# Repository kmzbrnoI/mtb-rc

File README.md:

MTB-RC – MTBbus RailCom detector
================================

MTB-RC is a RailCom detector sending addresses of a detected mobile decoders
via MTBbus.

## Features

* 8 track sections.
* [MTBbus v4](https://mtb.kmz-brno.cz/) interface.
* Reading DCC addresses of mobile decoders.
* Galvanic separation of MTB & DCC.
* Single STM32F103 main MCU.
* MTB part power input: 8-20 V.
* DCC part powered directly from DCC.
* Several IO & power protections (ESD, overvoltage, switched polarity, ...).
* 4->1 track time multiplexing.
* Opensource & openhardware design.

## PCB

See [README in `pcb` subfolder](pcb/README.md).

## Firmware

See [README in `fw` subfolder](fw/README.md).

## Authors

* Kateřina Hanáková
* [Jan Horáček](mailto:jan.horacek@kmz-brno.cz)

## Licence

See README in subfolders for licenses regarding pcb design and firmware.

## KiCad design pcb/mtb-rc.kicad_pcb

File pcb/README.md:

MTB-RC PCB
==========

## Design

Schematics & PCB are designed in KiCad 7.

## Production

PCB is prepared to be automatically assembled in [JLCPCB](https://jlcpcb.com/).
SMD parts on **bottom** side should be assembled. Each SMD part has its `LCSC_ITEM`
attribute set.

```bash
$ make fab
```

## License

Content of this directory is provided under [Creative Commons
Attribution-ShareAlike 4.0
License](https://creativecommons.org/licenses/by-sa/4.0/) as openhardware
project. You may download any data, contribute to the project, create PCB
yourself or even sell it yourself.

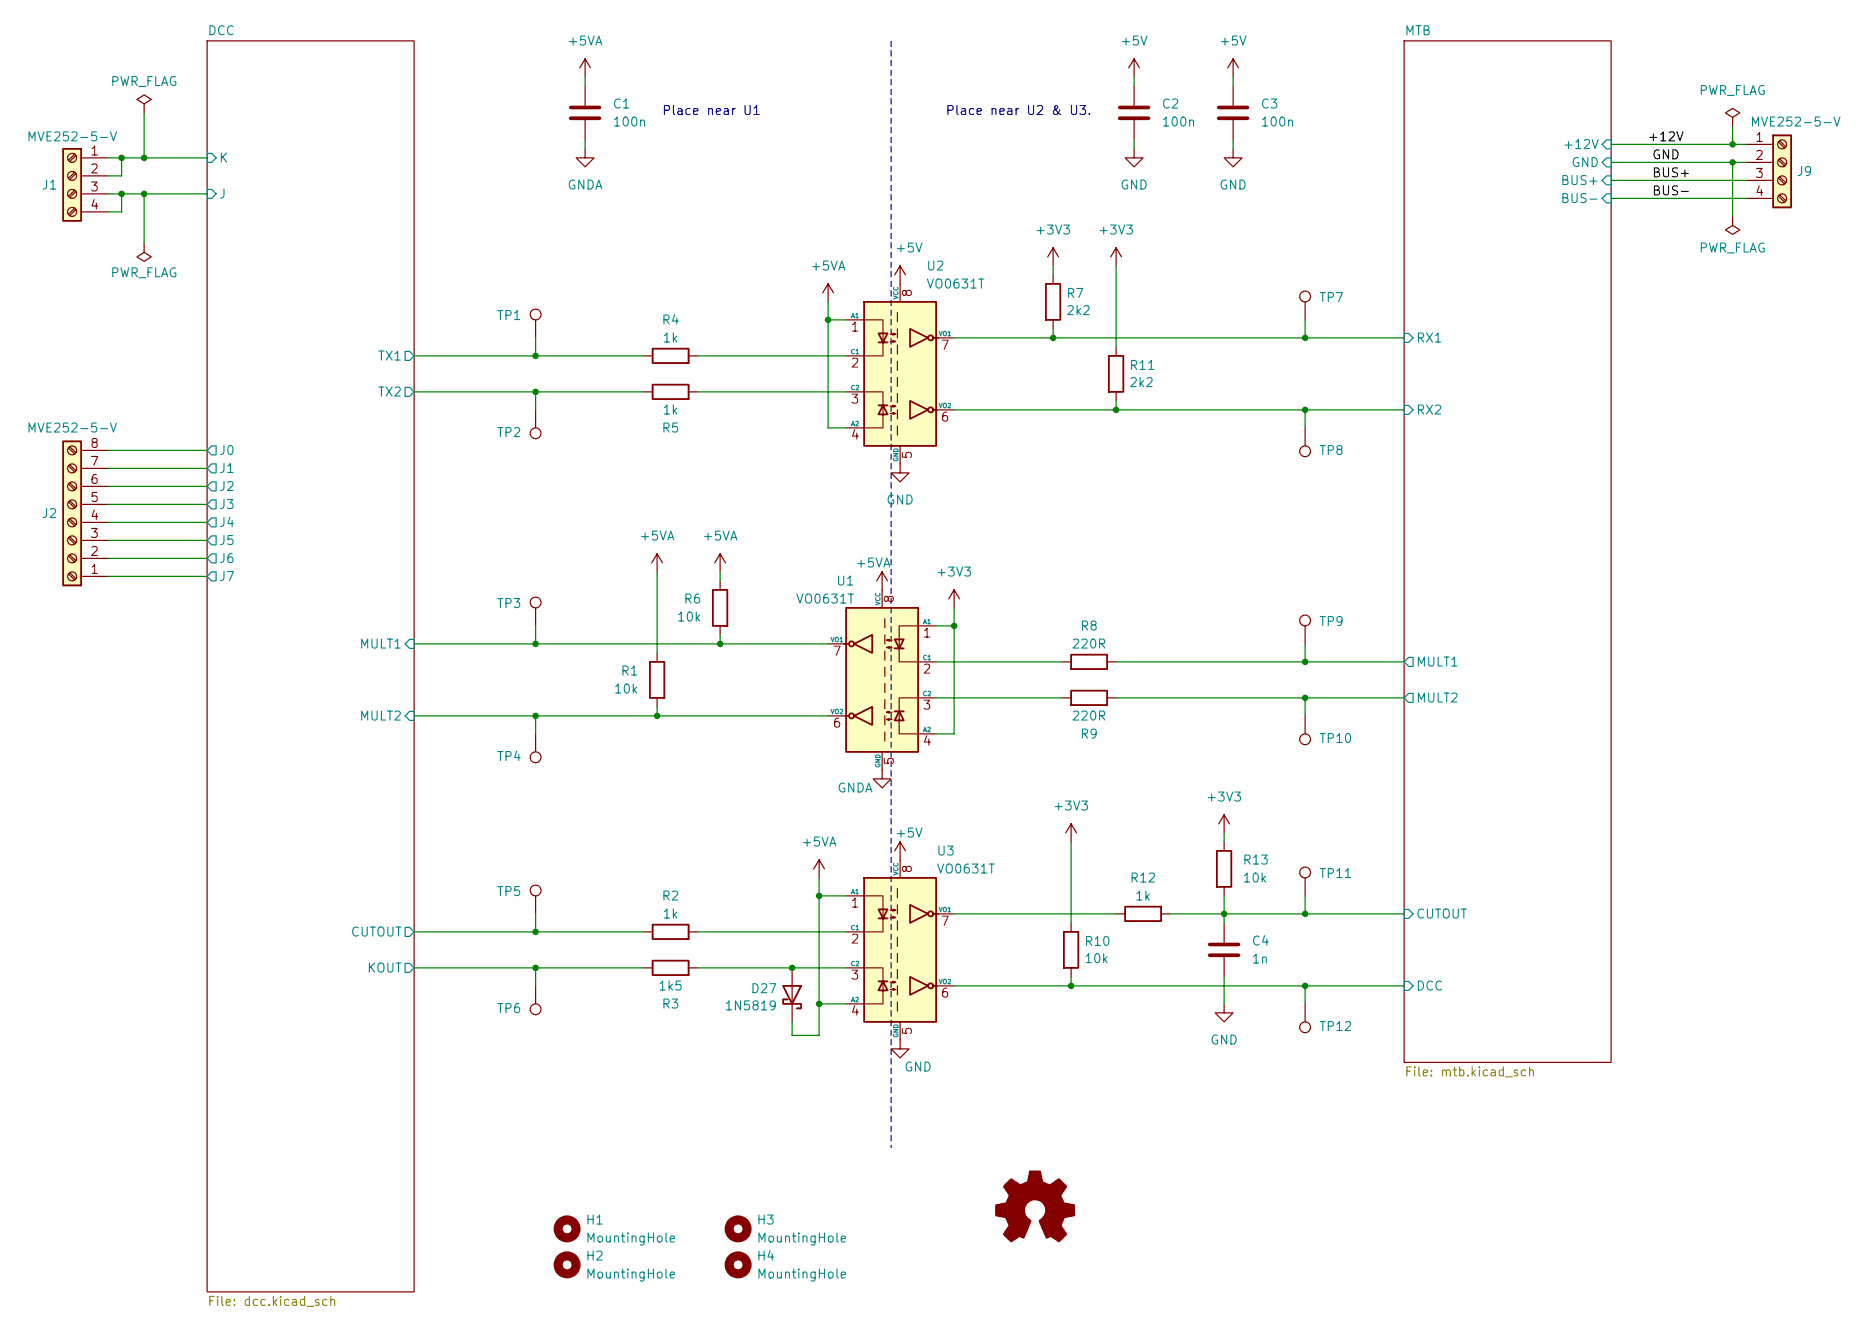
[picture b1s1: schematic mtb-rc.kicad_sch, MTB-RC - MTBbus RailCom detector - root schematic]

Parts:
C1, C2, C3: 100n; C_0805_2012Metric_Pad1.18x1.45mm_HandSolder
C4: 1n; C_0805_2012Metric_Pad1.18x1.45mm_HandSolder
D27: 1N5819; D_SOD-123
H1, H2, H3, H4: MountingHole; MountingHole_3.2mm_M3_Pad_Via
J1, J9: MVE252-5-V; MVE252-5-V-2x
J2: MVE252-5-V; MVE252-5-V-4x
R1, R6, R10, R13: 10k; R_0805_2012Metric_Pad1.20x1.40mm_HandSolder
R2, R4, R5, R12: 1k; R_0805_2012Metric_Pad1.20x1.40mm_HandSolder
R3: 1k5; R_0805_2012Metric_Pad1.20x1.40mm_HandSolder
R7, R11: 2k2; R_0805_2012Metric_Pad1.20x1.40mm_HandSolder
R8, R9: 220R; R_0805_2012Metric_Pad1.20x1.40mm_HandSolder
TP1, TP2, TP3, TP4, TP5, TP6, TP7, TP8, TP9, TP10, TP11, TP12: PinHeader_1x01_P2.54mm_Vertical
U1, U2, U3: VO0631T; SOIC-8_3.9x4.9mm_P1.27mm

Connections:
+3V3: R7.1, R10.1, R11.1, R13.1, U1.1 (A1), U1.4 (A2); also elsewhere on the board
+5V: C2.1, C3.1, U2.8 (VCC), U3.8 (VCC); also elsewhere on the board
+5VA: C1.1, D27.1 (K), R1.1, R6.1, U1.8 (VCC), U2.1 (A1), U2.4 (A2), U3.1 (A1), U3.4 (A2); also elsewhere on the board
/+12V: J9.1; also elsewhere on the board
/BUS+: J9.3; also elsewhere on the board
/BUS-: J9.4; also elsewhere on the board
/DCC/CUTOUT: R2.1, TP5.1; also elsewhere on the board
/DCC/J: J1.3, J1.4; also elsewhere on the board
/DCC/J0: J2.8; also elsewhere on the board
/DCC/J1: J2.7; also elsewhere on the board
/DCC/J2: J2.6; also elsewhere on the board
/DCC/J3: J2.5; also elsewhere on the board
/DCC/J4: J2.4; also elsewhere on the board
/DCC/J5: J2.3; also elsewhere on the board
/DCC/J6: J2.2; also elsewhere on the board
/DCC/J7: J2.1; also elsewhere on the board
/DCC/MULT1: R6.2, TP3.1, U1.7 (VO1); also elsewhere on the board
/DCC/MULT2: R1.2, TP4.1, U1.6 (VO2); also elsewhere on the board
/DCC/TX1: R4.1, TP1.1; also elsewhere on the board
/DCC/TX2: R5.1, TP2.1; also elsewhere on the board
/MTB/CUTOUT: C4.1, R12.2, R13.2, TP11.1; also elsewhere on the board
/MTB/DCC: R10.2, TP12.1, U3.6 (VO2); also elsewhere on the board
/MTB/MULT1: R8.1, TP9.1; also elsewhere on the board
/MTB/MULT2: R9.1, TP10.1; also elsewhere on the board
/MTB/RX1: R7.2, TP7.1, U2.7 (VO1); also elsewhere on the board
/MTB/RX2: R11.2, TP8.1, U2.6 (VO2); also elsewhere on the board
GND: C2.2, C3.2, C4.2, J9.2, U2.5 (GND), U3.5 (GND); also elsewhere on the board
GNDA: C1.2, U1.5 (GND); also elsewhere on the board
K: J1.1, J1.2; also elsewhere on the board
KOUT: R3.1, TP6.1; also elsewhere on the board
unnamed: D27.2 (A), R3.2, U3.3 (C2)
unnamed: R8.2, U1.2 (C1)
unnamed: R9.2, U1.3 (C2)
unnamed: R4.2, U2.2 (C1)
unnamed: R5.2, U2.3 (C2)
unnamed: R2.2, U3.2 (C1)
unnamed: R12.1, U3.7 (VO1)

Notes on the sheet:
Place near U2 & U3.
Place near U1

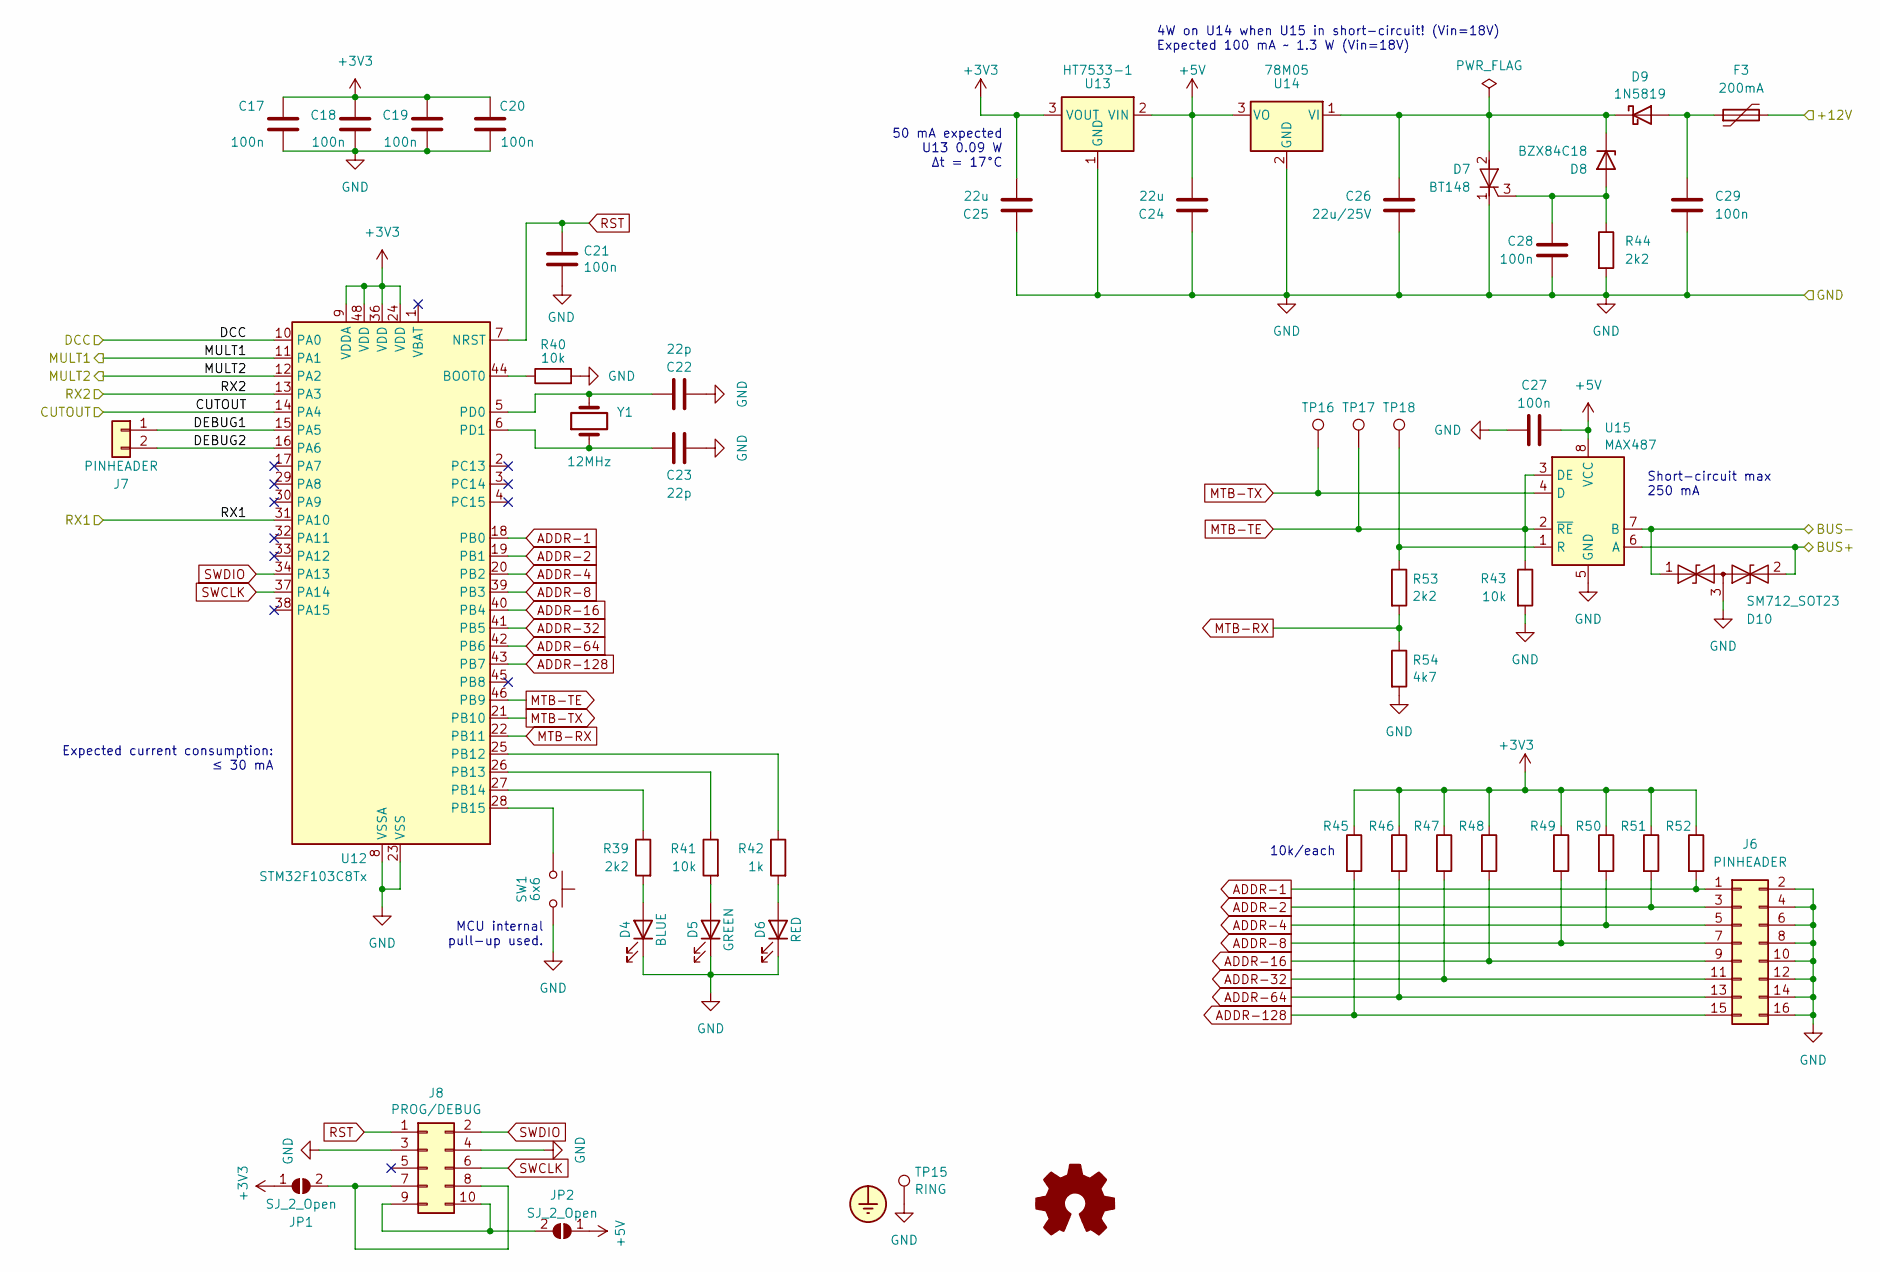
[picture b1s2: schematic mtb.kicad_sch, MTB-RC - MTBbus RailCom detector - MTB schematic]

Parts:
C17, C18, C19, C20, C27: 100n; C_0805_2012Metric_Pad1.18x1.45mm_HandSolder
C21: 100n; C_0805_2012Metric_Pad1.18x1.45mm_HandSolder; LCSC C49678
C22, C23: 22p; C_0805_2012Metric_Pad1.18x1.45mm_HandSolder
C24, C25: 22u; C_0805_2012Metric_Pad1.18x1.45mm_HandSolder
C26: 22u/25V; C_0805_2012Metric_Pad1.18x1.45mm_HandSolder
C28, C29: 100n; C_0805_2012Metric
D4: BLUE; LED_0805_2012Metric_Pad1.15x1.40mm_HandSolder
D5: GREEN; LED_0805_2012Metric_Pad1.15x1.40mm_HandSolder
D6: RED; LED_0805_2012Metric_Pad1.15x1.40mm_HandSolder
D7: BT148; SOT-223
D8: BZX84C18; SOT-23
D9: 1N5819; D_SOD-123
D10: SM712_SOT23; SOT-23
F3: 200mA; Fuse_1812_4532Metric_Pad1.30x3.40mm_HandSolder
J6: PINHEADER; PinHeader_2x08_P2.54mm_Vertical
J7: PINHEADER; PinHeader_1x02_P2.54mm_Vertical
J8: PROG/DEBUG; PinHeader_2x05_P2.54mm_Vertical; JLCPCB_IGNORE true
JP1, JP2: SJ_2_Open; PinHeader_1x02_P2.54mm_Vertical; JLCPCB_IGNORE true
R39, R44, R53: 2k2; R_0805_2012Metric_Pad1.20x1.40mm_HandSolder
R40, R41, R43, R45, R46, R47, R48, R49, R50, R51, R52: 10k; R_0805_2012Metric_Pad1.20x1.40mm_HandSolder
R42: 1k; R_0805_2012Metric_Pad1.20x1.40mm_HandSolder
R54: 4k7; R_0805_2012Metric_Pad1.20x1.40mm_HandSolder
SW1: 6x6; SW_PUSH_6mm_H4.3mm
TP15: RING; TestPoint_Loop_D1.80mm_Drill1.0mm_Beaded
TP16, TP17, TP18: PAD; PinHeader_1x01_P2.54mm_Vertical
U12: STM32F103C8Tx; LQFP-48_7x7mm_P0.5mm
U13: HT7533-1; SOT-89-3_Handsoldering
U14: 78M05; TO-252-2
U15: MAX487; DIP-8_W7.62mm_LongPads
Y1: 12MHz; Crystal_HC49-U_Vertical

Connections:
+3V3: C17.1, C18.1, C19.1, C20.1, C25.2, JP1.1 (A), R45.1, R46.1, R47.1, R48.1, R49.1, R50.1, R51.1, R52.1, U12.9 (VDDA), U12.24 (VDD), U12.36 (VDD), U12.48 (VDD), U13.3 (VOUT); also elsewhere on the board
+5V: C24.2, C27.1, JP2.1 (A), U13.2 (VIN), U14.3 (VO), U15.8 (VCC); also elsewhere on the board
/+12V: F3.2; also elsewhere on the board
/BUS+: D10.2 (A2), U15.6 (A); also elsewhere on the board
/BUS-: D10.1 (A1), U15.7 (B); also elsewhere on the board
/MTB/CUTOUT: U12.14 (PA4); also elsewhere on the board
/MTB/DCC: U12.10 (PA0); also elsewhere on the board
/MTB/DEBUG1: J7.1, U12.15 (PA5)
/MTB/DEBUG2: J7.2, U12.16 (PA6)
/MTB/MULT1: U12.11 (PA1); also elsewhere on the board
/MTB/MULT2: U12.12 (PA2); also elsewhere on the board
/MTB/RX1: U12.31 (PA10); also elsewhere on the board
/MTB/RX2: U12.13 (PA3); also elsewhere on the board
ADDR-1: J6.1, R52.2, U12.18 (PB0)
ADDR-2: J6.3, R51.2, U12.19 (PB1)
ADDR-4: J6.5, R50.2, U12.20 (PB2)
ADDR-8: J6.7, R49.2, U12.39 (PB3)
ADDR-16: J6.9, R48.2, U12.40 (PB4)
ADDR-32: J6.11, R47.2, U12.41 (PB5)
ADDR-64: J6.13, R46.2, U12.42 (PB6)
ADDR-128: J6.15, R45.2, U12.43 (PB7)
GND: C17.2, C18.2, C19.2, C20.2, C21.1, C22.2, C23.2, C24.1, C25.1, C26.2, C27.2, C28.2, C29.2, D4.1 (K), D5.1 (K), D6.1 (K), D7.1 (K), D10.3 (common), J6.2, J6.4, J6.6, J6.8, J6.10, J6.12, J6.14, J6.16, J8.3, J8.4, R40.2, R43.2, R44.2, R54.2, SW1.1, TP15.1, U12.8 (VSSA), U12.23 (VSS), U12.35 (VSS), U12.47 (VSS), U13.1 (GND), U14.2 (GND), U15.5 (GND); also elsewhere on the board
MTB-RX: R53.2, R54.1, U12.22 (PB11)
MTB-TE: R43.1, TP17.1, U12.46 (PB9), U15.2 (~RE), U15.3 (DE)
MTB-TX: TP16.1, U12.21 (PB10), U15.4 (D)
unnamed: D4.2 (A), R39.2
unnamed: D5.2 (A), R41.2
unnamed: D6.2 (A), R42.2
unnamed: C26.1, D7.2 (A), D8.3 (K), D9.1 (K), U14.1 (VI)
unnamed: C28.1, D7.3 (G), D8.1 (A), R44.1
unnamed: C29.1, D9.2 (A), F3.1
unnamed: J8.7, J8.8, JP1.2 (B)
unnamed: J8.9, J8.10, JP2.2 (B)
unnamed: R40.1, U12.44 (BOOT0)
unnamed: R42.1, U12.25 (PB12)
unnamed: R41.1, U12.26 (PB13)
unnamed: R39.1, U12.27 (PB14)
unnamed: SW1.2, U12.28 (PB15)
unnamed: C22.1, U12.5 (PD0), Y1.2
unnamed: C23.1, U12.6 (PD1), Y1.1
unnamed: R53.1, TP18.1, U15.1 (R)
RST: C21.2, J8.1, U12.7 (NRST)
SWCLK: J8.6, U12.37 (PA14)
SWDIO: J8.2, U12.34 (PA13)

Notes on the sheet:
4W on U14 when U15 in short-circuit! (Vin=18V) Expected 100 mA ~ 1.3 W (Vin=18V)
Expected current consumption: ≤ 30 mA
50 mA expected U13 0.09 W Δt = 17°C
10k/each
Short-circuit max 250 mA
MCU internal pull-up used.

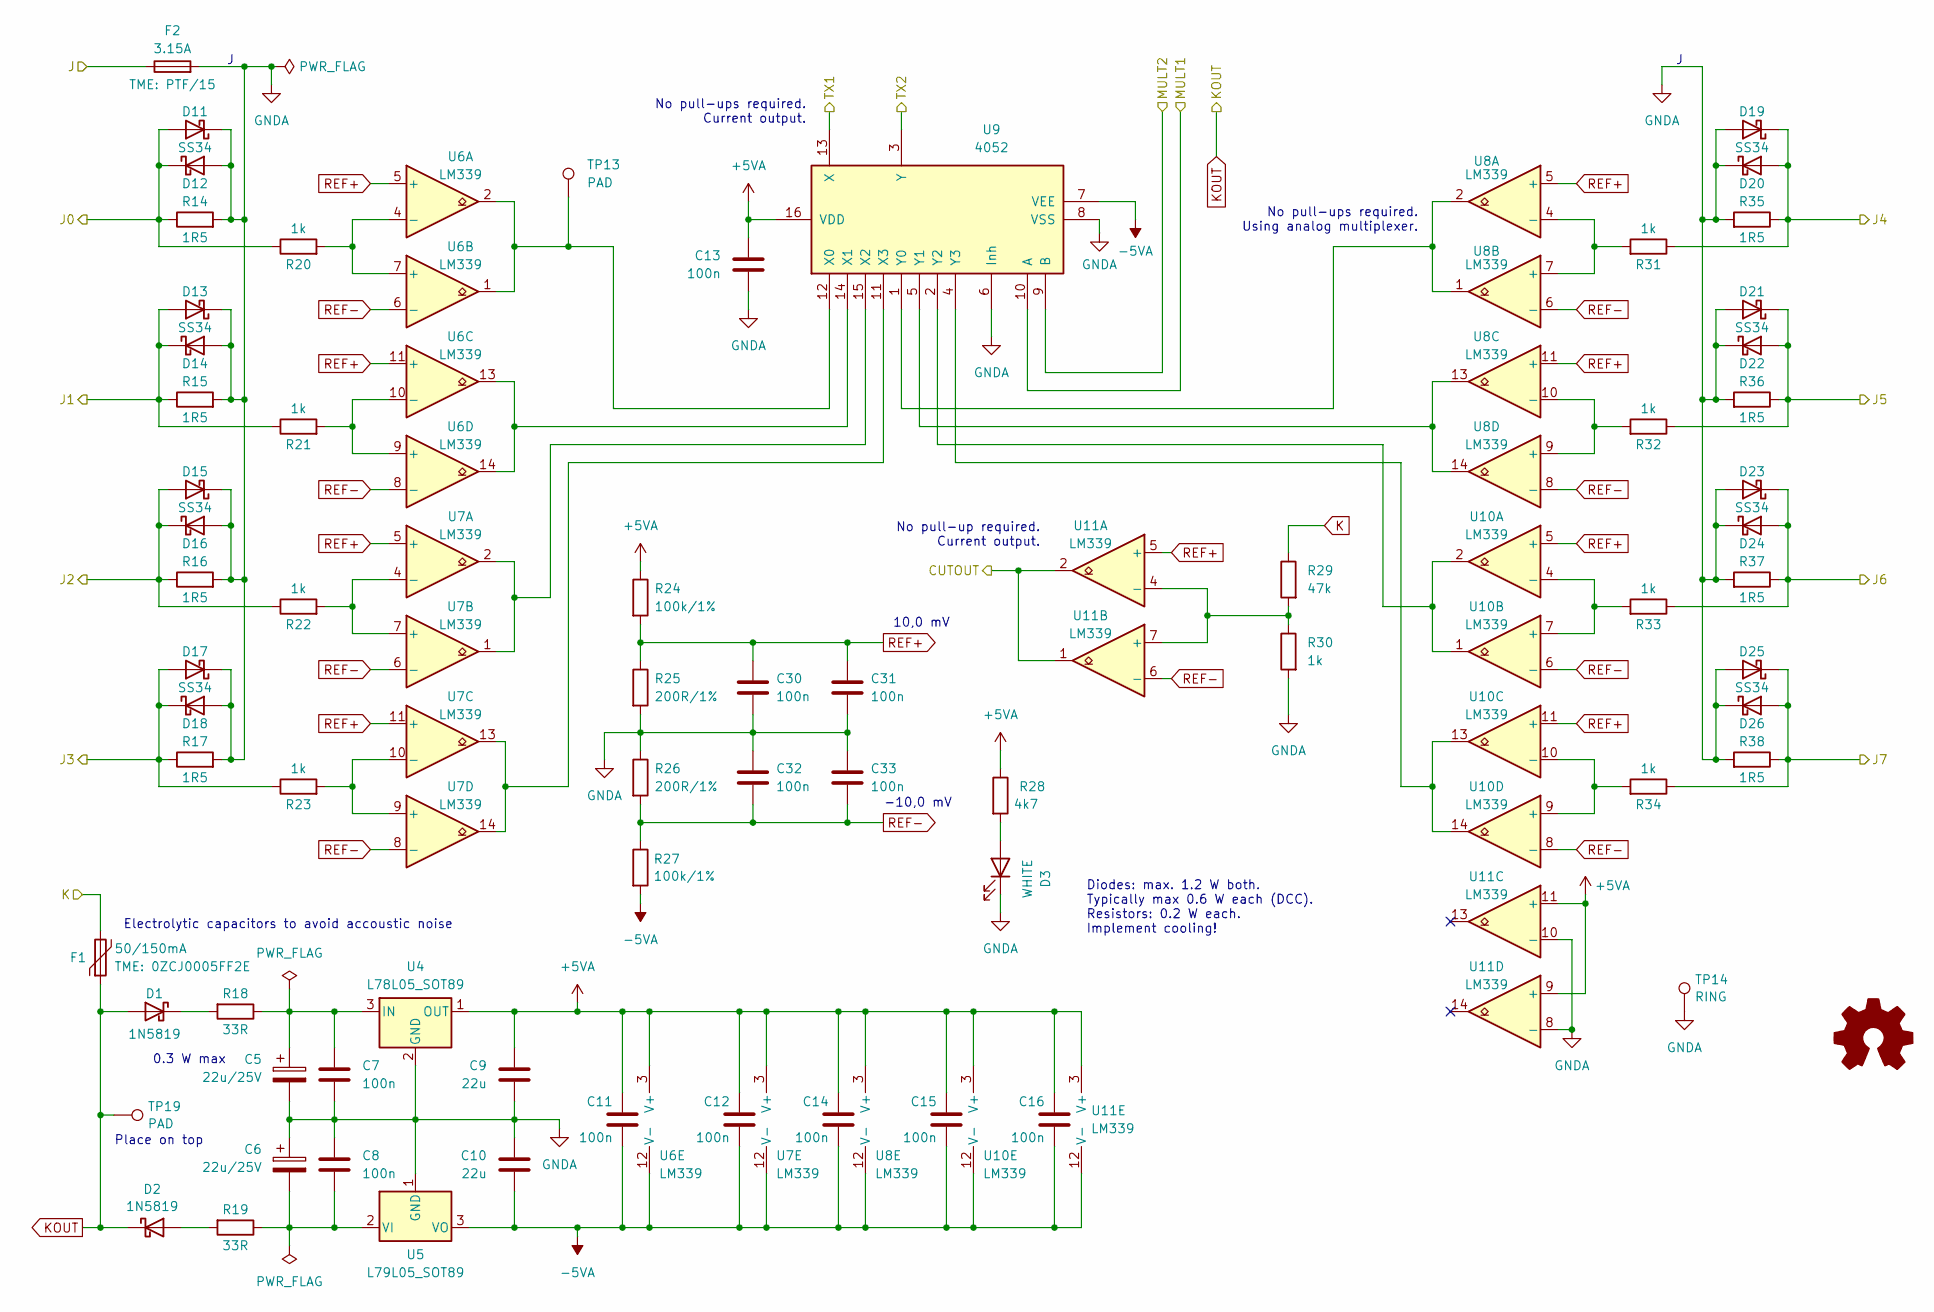
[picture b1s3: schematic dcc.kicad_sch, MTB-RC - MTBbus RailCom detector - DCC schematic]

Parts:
C5, C6: 22u/25V; CP_Radial_D5.0mm_P2.00mm
C7, C8, C30, C32: 100n; C_0805_2012Metric_Pad1.18x1.45mm_HandSolder
C9, C10: 22u; C_0805_2012Metric_Pad1.18x1.45mm_HandSolder
C11, C12, C13, C14, C15, C16, C31, C33: 100n; C_0805_2012Metric
D1, D2: 1N5819; D_SOD-123
D3: WHITE; LED_0805_2012Metric_Pad1.15x1.40mm_HandSolder
D11, D12, D13, D14, D15, D16, D17, D18, D19, D20, D21, D22, D23, D24, D25, D26: SS34; D_SMA_Handsoldering
F1: 50/150mA; Fuse_1206_3216Metric_Pad1.42x1.75mm_HandSolder
F2: 3.15A; Fuseholder_Cylinder-5x20mm_Stelvio-Kontek_PTF78_Horizontal_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
R14, R15, R16, R17, R35, R36, R37, R38: 1R5; R_2512_6332Metric_Pad1.40x3.35mm_HandSolder
R18, R19: 33R; R_2512_6332Metric_Pad1.40x3.35mm_HandSolder
R20, R21, R22, R23, R30, R31, R32, R33, R34: 1k; R_0805_2012Metric
R24, R27: 100k/1%; R_0805_2012Metric_Pad1.20x1.40mm_HandSolder
R25, R26: 200R/1%; R_0805_2012Metric_Pad1.20x1.40mm_HandSolder
R28: 4k7; R_0805_2012Metric_Pad1.20x1.40mm_HandSolder
R29: 47k; R_0805_2012Metric
TP13, TP19: PAD; TestPoint_Pad_D2.0mm
TP14: RING; TestPoint_Loop_D1.80mm_Drill1.0mm_Beaded
U4: L78L05_SOT89; SOT-89-3
U5: L79L05_SOT89; SOT-89-3
U6, U7, U8, U10, U11: LM339; SO-14_3.9x8.65mm_P1.27mm
U9: 4052; SO-16_3.9x9.9mm_P1.27mm

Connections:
+5VA: C9.1, C11.1, C12.1, C13.1, C14.1, C15.1, C16.1, R24.1, R28.1, U4.1 (OUT), U6.3 (V+), U7.3 (V+), U8.3 (V+), U9.16 (VDD), U10.3 (V+), U11.3 (V+), U11.9 (+), U11.11 (+); also elsewhere on the board
-5VA: C10.2, C11.2, C12.2, C14.2, C15.2, C16.2, R27.2, U5.3 (VO), U6.12 (V-), U7.12 (V-), U8.12 (V-), U9.7 (VEE), U10.12 (V-), U11.12 (V-)
/DCC/CUTOUT: U11.1, U11.2; also elsewhere on the board
/DCC/J: F2.1; also elsewhere on the board
/DCC/J0: D11.2 (A), D12.1 (K), R14.1, R20.1; also elsewhere on the board
/DCC/J1: D13.2 (A), D14.1 (K), R15.1, R21.1; also elsewhere on the board
/DCC/J2: D15.2 (A), D16.1 (K), R16.1, R22.1; also elsewhere on the board
/DCC/J3: D17.2 (A), D18.1 (K), R17.1, R23.1; also elsewhere on the board
/DCC/J4: D19.1 (K), D20.2 (A), R31.1, R35.1; also elsewhere on the board
/DCC/J5: D21.1 (K), D22.2 (A), R32.1, R36.1; also elsewhere on the board
/DCC/J6: D23.1 (K), D24.2 (A), R33.1, R37.1; also elsewhere on the board
/DCC/J7: D25.1 (K), D26.2 (A), R34.1, R38.1; also elsewhere on the board
/DCC/MULT1: U9.10 (A); also elsewhere on the board
/DCC/MULT2: U9.9 (B); also elsewhere on the board
/DCC/TX1: U9.13 (X); also elsewhere on the board
/DCC/TX2: U9.3 (Y); also elsewhere on the board
GNDA: C5.2, C6.1, C7.2, C8.1, C9.2, C10.1, C13.2, C30.2, C31.2, C32.1, C33.1, D3.1 (K), D11.1 (K), D12.2 (A), D13.1 (K), D14.2 (A), D15.1 (K), D16.2 (A), D17.1 (K), D18.2 (A), D19.2 (A), D20.1 (K), D21.2 (A), D22.1 (K), D23.2 (A), D24.1 (K), D25.2 (A), D26.1 (K), F2.2, R14.2, R15.2, R16.2, R17.2, R25.2, R26.1, R30.2, R35.2, R36.2, R37.2, R38.2, TP14.1, U4.2 (GND), U5.1 (GND), U9.6 (Inh), U9.8 (VSS), U11.8 (-), U11.10 (-); also elsewhere on the board
K: F1.2, R29.1; also elsewhere on the board
KOUT: D1.2 (A), D2.1 (K), F1.1, TP19.1; also elsewhere on the board
unnamed: D1.1 (K), R18.2
unnamed: D2.2 (A), R19.2
unnamed: D3.2 (A), R28.2
unnamed: C5.1, C7.1, R18.1, U4.3 (IN)
unnamed: C6.2, C8.2, R19.1, U5.2 (VI)
unnamed: R20.2, U6.4 (-), U6.7 (+)
unnamed: R21.2, U6.9 (+), U6.10 (-)
unnamed: R22.2, U7.4 (-), U7.7 (+)
unnamed: R23.2, U7.9 (+), U7.10 (-)
unnamed: R31.2, U8.4 (-), U8.7 (+)
unnamed: R32.2, U8.9 (+), U8.10 (-)
unnamed: TP13.1, U6.1, U6.2, U9.12 (X0)
unnamed: U6.13, U6.14, U9.14 (X1)
unnamed: U7.1, U7.2, U9.15 (X2)
unnamed: U7.13, U7.14, U9.11 (X3)
unnamed: U8.1, U8.2, U9.1 (Y0)
unnamed: U8.13, U8.14, U9.5 (Y1)
unnamed: U9.2 (Y2), U10.1, U10.2
unnamed: U9.4 (Y3), U10.13, U10.14
unnamed: R33.2, U10.4 (-), U10.7 (+)
unnamed: R34.2, U10.9 (+), U10.10 (-)
unnamed: R29.2, R30.1, U11.4 (-), U11.7 (+)
REF+: C30.1, C31.1, R24.2, R25.1, U6.5 (+), U6.11 (+), U7.5 (+), U7.11 (+), U8.5 (+), U8.11 (+), U10.5 (+), U10.11 (+), U11.5 (+)
REF-: C32.2, C33.2, R26.2, R27.1, U6.6 (-), U6.8 (-), U7.6 (-), U7.8 (-), U8.6 (-), U8.8 (-), U10.6 (-), U10.8 (-), U11.6 (-)

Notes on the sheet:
10,0 mV
No pull-ups required. Current output.
Diodes: max. 1.2 W both. Typically max 0.6 W each (DCC). Resistors: 0.2 W each. Implement cooling!
No pull-ups required. Using analog multiplexer.
Place on top
Electrolytic capacitors to avoid accoustic noise
0.3 W max
No pull-up required. Current output.
-10,0 mV

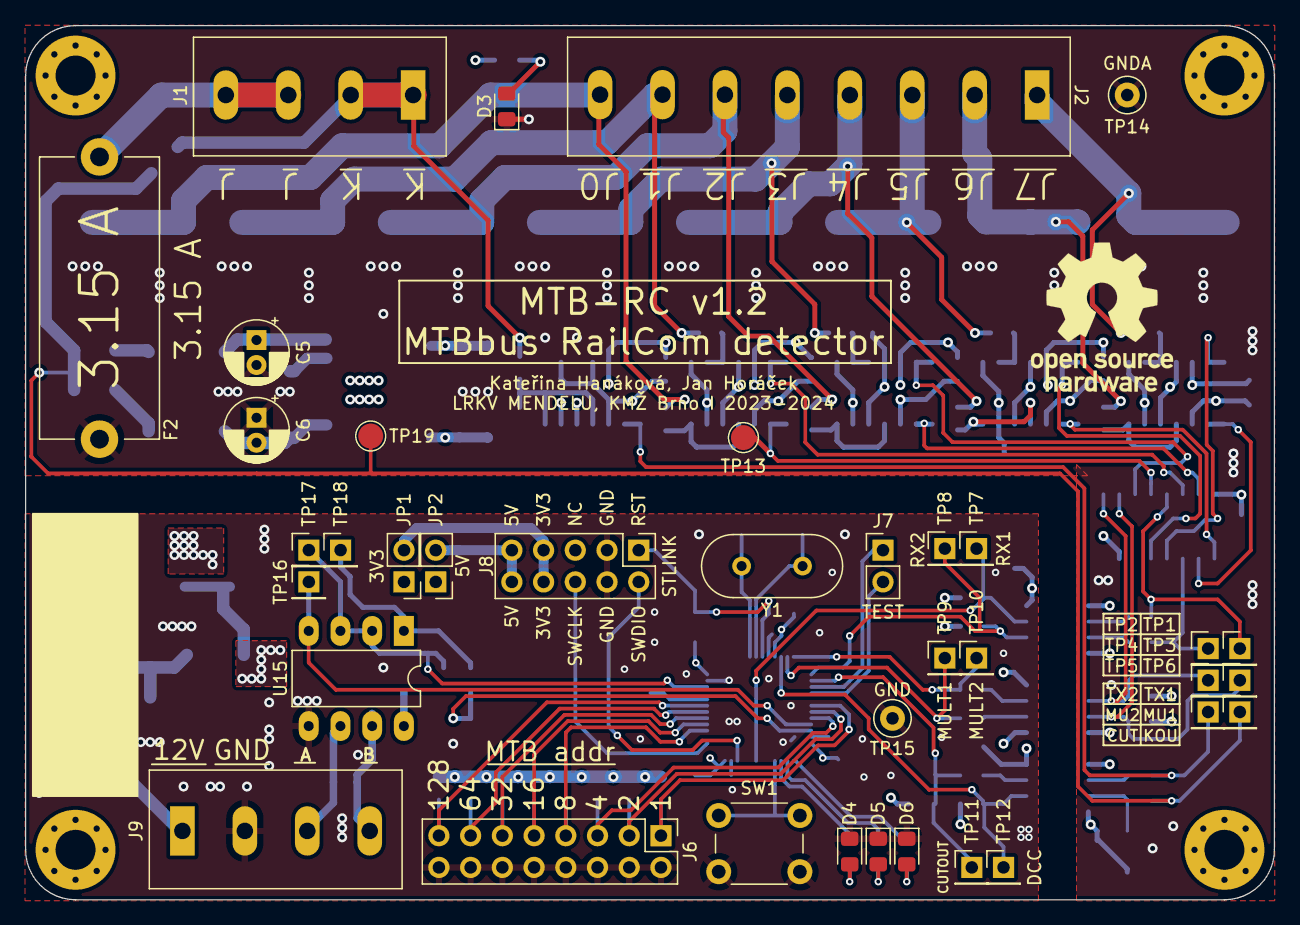
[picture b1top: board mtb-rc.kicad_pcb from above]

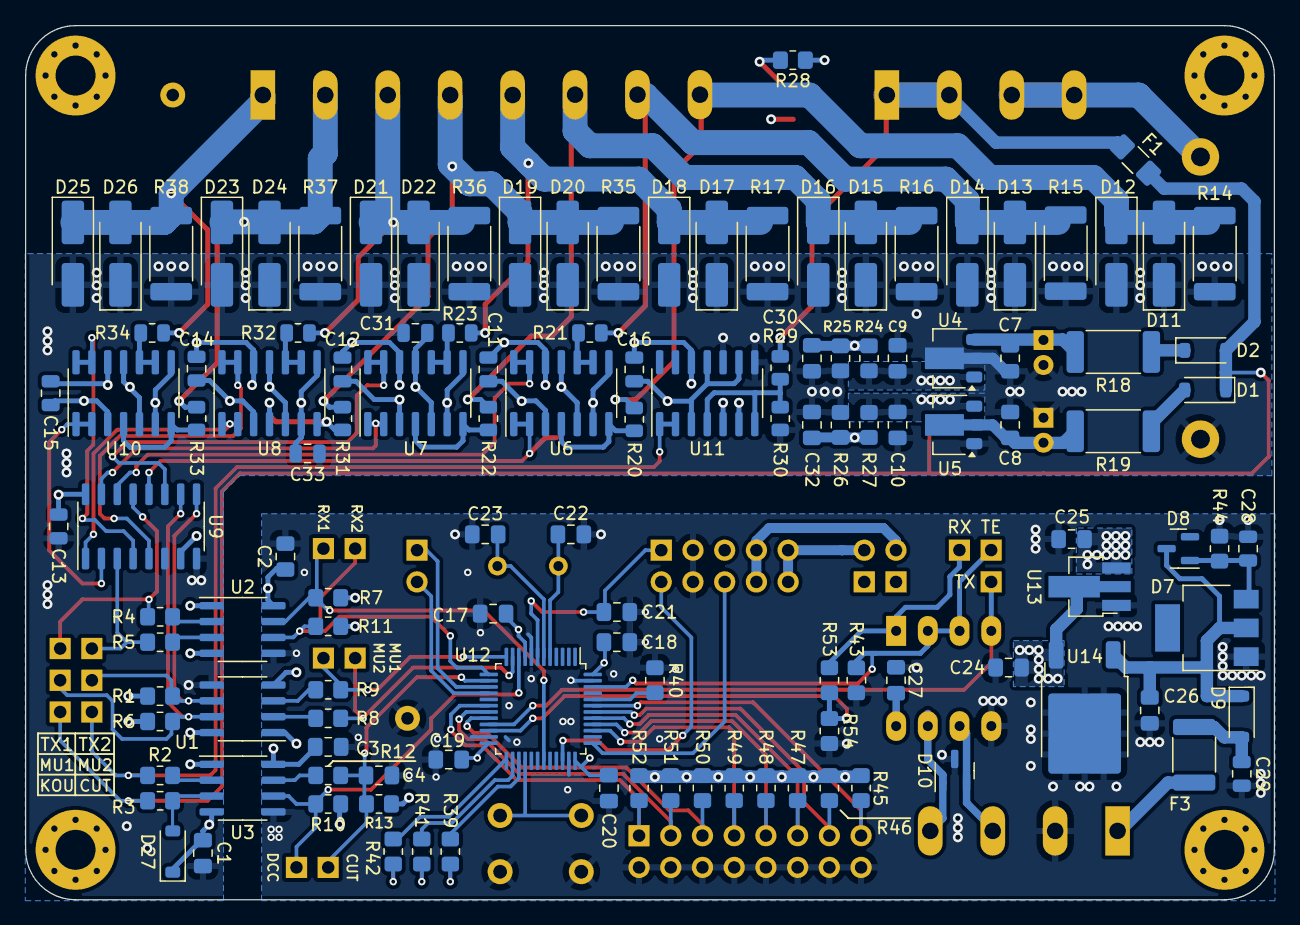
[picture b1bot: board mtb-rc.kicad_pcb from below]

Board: 4 copper layers, 100.0 x 70.0 mm, 165 parts (124 on the bottom side), 94 nets.

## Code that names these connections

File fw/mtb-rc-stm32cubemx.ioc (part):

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Mcu.Name=STM32F103C(8-B)Tx
Mcu.Package=LQFP48
Mcu.UserName=STM32F103C8Tx
PA0-WKUP.GPIOParameters=GPIO_Label
PA0-WKUP.GPIO_Label=DCC
PA0-WKUP.Signal=S_TIM2_CH1_ETR
PA1.GPIOParameters=GPIO_Speed,GPIO_Label
PA1.GPIO_Label=MULT1
PA1.GPIO_Speed=GPIO_SPEED_FREQ_MEDIUM
PA1.Signal=GPIO_Output
PA10.GPIOParameters=GPIO_Label
PA10.GPIO_Label=RC1_RX
PA10.Mode=Asynchronous
PA10.Signal=USART1_RX
PA12.Signal=S_TIM1_ETR
PA13.Mode=Serial_Wire
PA13.Signal=SYS_JTMS-SWDIO
PA14.Mode=Serial_Wire
PA14.Signal=SYS_JTCK-SWCLK
PA2.Mode=Asynchronous
PA2.Signal=USART2_TX
PA3.GPIOParameters=GPIO_Label
PA3.GPIO_Label=RC2_RX
PA3.Mode=Asynchronous
PA3.Signal=USART2_RX
PA4.GPIOParameters=GPIO_Label,GPIO_ModeDefaultEXTI
PA4.GPIO_Label=CUTOUT
PA4.GPIO_ModeDefaultEXTI=GPIO_MODE_IT_RISING_FALLING
PA4.Signal=GPXTI4
PA5.GPIOParameters=GPIO_Label
PA5.GPIO_Label=DEBUG1
PA5.Signal=GPIO_Output
PA6.GPIOParameters=GPIO_Label
PA6.GPIO_Label=DEBUG2
PA6.Signal=GPIO_Output
PA9.Mode=Asynchronous
PA9.Signal=USART1_TX
PB0.GPIOParameters=GPIO_Label
PB0.GPIO_Label=ADDR1
PB0.Signal=GPIO_Input
PB1.GPIOParameters=GPIO_Label
PB1.GPIO_Label=ADDR2
PB1.Signal=GPIO_Input
PB10.GPIOParameters=GPIO_Label
PB10.GPIO_Label=MTB_TX
PB10.Mode=Asynchronous
PB10.Signal=USART3_TX
PB11.GPIOParameters=GPIO_Label
PB11.GPIO_Label=MTB_RX
PB11.Mode=Asynchronous
PB11.Signal=USART3_RX
PB12.GPIOParameters=GPIO_Label
PB12.GPIO_Label=LED_RED
PB12.Signal=GPIO_Output
PB13.GPIOParameters=GPIO_Label
PB13.GPIO_Label=LED_GREEN
PB13.Signal=GPIO_Output
PB14.GPIOParameters=GPIO_Label
PB14.GPIO_Label=LED_BLUE
PB14.Signal=GPIO_Output
PB15.GPIOParameters=GPIO_PuPd,GPIO_Label
PB15.GPIO_Label=BUTTON
PB15.GPIO_PuPd=GPIO_PULLUP
PB15.Signal=GPIO_Input
PB2.GPIOParameters=GPIO_Label
PB2.GPIO_Label=ADDR4
PB2.Signal=GPIO_Input
PB3.GPIOParameters=GPIO_Label
PB3.GPIO_Label=ADDR8
PB3.Signal=GPIO_Input
PB4.GPIOParameters=GPIO_Label
PB4.GPIO_Label=ADDR16
PB4.Signal=GPIO_Input
PB5.GPIOParameters=GPIO_Label
PB5.GPIO_Label=ADDR32
PB5.Signal=GPIO_Input
PB6.GPIOParameters=GPIO_Label
PB6.GPIO_Label=ADDR64
PB6.Signal=GPIO_Input
PB7.GPIOParameters=GPIO_Label
PB7.GPIO_Label=ADDR128
PB7.Signal=GPIO_Input
PB9.GPIOParameters=GPIO_Speed,GPIO_Label
PB9.GPIO_Label=MTB_TE
PB9.GPIO_Speed=GPIO_SPEED_FREQ_HIGH
PB9.Signal=GPIO_Output
PD0-OSC_IN.Mode=HSE-External-Oscillator
PD0-OSC_IN.Signal=RCC_OSC_IN
PD1-OSC_OUT.Mode=HSE-External-Oscillator
PD1-OSC_OUT.Signal=RCC_OSC_OUT
RCC.HSE_VALUE=12000000
RCC.SYSCLKFreq_VALUE=48000000
RCC.SYSCLKSource=RCC_SYSCLKSOURCE_PLLCLK
board=custom

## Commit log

2023-03-20 zkouška
    vyzkoušení a seznámení s Kicad
2023-04-06 Add mooster schematics.
2023-07-11 mooster -> pcb, add fw directory.
2023-10-05 Move mooster to mooster directory.
2023-10-05 Add first shcematics.
2023-10-05 Wires adresses, add capacitors to MCU.
2023-10-05 Add power supply.
2023-10-05 Wire MTB bus driver.
2023-10-05 Finished MTB part.
2023-10-05 DCC WIP.
2023-10-08 Some adjustments with comparators.
2023-10-10 Updated DCC part.
2023-10-11 Some changes in dcc part.
2023-10-12 Added power stabilization in DCC.
2023-10-12 Finished DCC part.
2023-10-12 Connect DCC and MTB parts.
2023-10-12 Finished.
2023-10-23 Added description.
2023-10-23 Added testpoints.
2023-10-23 Make ERC PASS.
2023-10-23 Added some footprints.
2023-10-28 Resistors added from 24.10.
2023-10-28 Added Sch.diodes, text editing..
2023-10-29 Edited resistors in MTB part.
2023-10-29 Resistors values edited in mtb part.
2023-10-29 eddited again.
2023-11-12 Added Schottky in DCC part and fuse footprint.
2023-11-12 Added values schottky.
2023-11-14 Minor realign of new Schottkys.
2023-11-23 Remove mooster (outdated).
2023-11-23 root: rotate test points same way.
2023-11-23 Add several notes.
2023-11-23 Add rest of footprints.
2023-11-23 Make TME attributes visible.
2023-12-07 Update note regarding diode thermal loss.
2023-12-07 PCB WIP.
2023-12-07 pcb: wire multiplexors.
2023-12-07 pcb: wire dcc voltage stabilization.
2023-12-09 pcb: wire multiplexer's inputs.
2023-12-09 Add filled zone to MTB part.
2023-12-09 pcb: use THT testpins for DCC part.
2023-12-09 pcb: everything routed.
2023-12-10 Use handsolder SMDs where possible.
2023-12-10 pcb: silkscreen top.
2023-12-10 pcb: silkscreen.
2023-12-10 Use SOT83-handsolder for DCC part.
2023-12-10 Pcb tweaks.
2023-12-10 Add empty README.
2023-12-10 Wire empty inputs of U11.
2023-12-10 Use smaller pull-ups for RailCom RX.
2023-12-10 Tweak optocoupler LED current.
2023-12-10 VEE of 4052 to -5VA.
2023-12-10 Use MAX478 as a MTBbus driver.
2023-12-11 Use double J & K connectors.
2023-12-11 78L05 -> 78M05. AMS1113-3.3 -> HT7533.
2023-12-11 Add RS485 level shifting.
2023-12-11 Resolve some DRC issues.
2023-12-12 MTB: couple 3V3 stabilizer serially with 5V stabilizer.
2023-12-12 railcomdet -> MTB-RC.
2023-12-13 w=11cm -> w=10cm.
2023-12-13 Resolve DRC issues.
2023-12-13 Minor tweaks.
2023-12-14 More space for STlink connector.
2023-12-14 Add explanatory texts.
2023-12-17 Cleanup tracks & vias.
2023-12-17 Remove unused pads & vias.
2023-12-17 Run DRC, add exclusions.
2023-12-26 Use 2×MVE252-5-V footprint.
    To avoid DRC issues in PCB.
2023-12-26 v1.0 -> v1.1.
2023-12-28 Add root & PCB readmes.
2023-12-28 Add STM32CubeMX generated & tweaked empty project.
2023-12-28 Add other files for FW development.
2023-12-28 Add STM32CubeMX configuration file.
2023-12-30 Simplify generated source files.
2023-12-30 Use c99.
2023-12-30 Move mtbbus init & deinit & interrupts to separate files
2023-12-30 Add gpio.[ch].
2023-12-30 Add railcom.[ch].
2023-12-30 Tweak main.[ch].
2023-12-30 Shortly turn on LEDs at startup.
2023-12-31 J1-J8 -> J0-J7.
2024-01-02 Use 4×MVE252-5-V footprint.
    To avoid DRC issues in schematics.
2024-01-12 R40: fix orientation.
2024-01-13 Add optocoupler-led protection diode. Close #1.
2024-01-13 Remove "PAD" value of testpads where pads are not used.
2024-01-14 Use 12 MHz oscillator, internal freq=48 MHz.
2024-01-16 Use 12MHz oscillator.
2024-01-20 Use THT electrolytic capacitors for DCC stabilization.
    22uF/25V tantalum capacitors are too big.
2024-03-03 Enable assert.
2024-03-09 Add crc16modbus.[ch].
2024-03-09 Use most local assert instead of return values.
    So the error could be distinguished at the most-specific level (__FILE__, __LINE__).
2024-03-09 Import mtbbus.[ch] from mtb-uni-4-fw.
2024-03-09 Fix RX/TX/TE silkscreen positions.
2024-03-09 Add MTBbus driver.
2024-03-09 Setup TIM2 @ 10 ms.
2024-03-09 Move mtbbus files to 'mtbbus' directory.
2024-03-09 Add persistent storage for configuration.
    EEPROM emulated with internal flash.
2024-03-09 Use 'gpio' prefix for gpio functions.
2024-03-10 Add MTBbus address reading.
2024-03-10 Add proper LEDs handling.
2024-03-10 Add button debouncing & handling.
2024-03-10 Respond to required MTBbus messages.
2024-03-14 Add features to README.
2024-03-16 railcom -> railcom_ll.
2024-03-16 RC LL: make receiving work.
2024-03-16 RC: initialize UART.
2024-03-16 Add CUTOUT edge interrupt.
2024-03-16 RC LL: add timer for cutout length counting.
2024-03-16 Remove redundant TIMx initialization.
2024-03-16 Add railcom_ll api.
2024-03-16 RC LL: make usart2 work.
2024-03-16 Add railcom_addrs.[ch].
2024-03-16 Implement sending of detected addresses to MTBbus.
2024-03-16 Add railcom data protection table.
2024-03-16 Fix silly bug :).
2024-03-16 Add railcom middleware.
2024-03-17 Implement track multiplexing.
    Track is changed each 100 ms (400 ms whole cycle).
2024-03-21 Move railcom sources to 'railcom' directory.
2024-03-21 Add dcc parsing template.
2024-03-21 Add DCC edge interrupt.
2024-04-01 Use timer2 for DCC parsing.
2024-04-01 Implement low-level DCC parsing.
2024-04-01 Implement address reading based on data in channel 2.
2024-04-07 Typo, unify code style.
2024-04-07 Send basic DVs.
2024-04-07 RCLL: record diagnostic values.
2024-04-10 Send all RailCom LL DVs.
2024-04-10 Add RC MW diagnostics.
2024-04-10 Log also how many ch1 address was "added or updated".
2024-04-10 Initialize addr.
    Because of deterministic counters addr[12]_received_count_resets.
2024-04-11 Add protection against old data accumulation.
2024-04-11 Resolve crosstask problem.
2024-04-11 Add DCC diagnostics.
2024-04-11 Add MtbBus diagnostics.
2024-04-27 Remove unused defines.
2024-04-27 dcc_ll: resolve SWexla mismatch.
2024-04-27 Resolve TODOs.
2024-04-27 mtbbus: use DMA for TX.
    Spare processor time in interrupts in IT mode.
2024-04-29 Unify TP4 orientation.
2024-05-18 R28 1k -> 4k7 (LED).
2024-05-23 Sch: slightly move wires.
2024-05-23 Add REF+/- capacitors C30, C31, C32, C33.
    These capacitors filter out any disturbances in REF+ & REF- signals.
2024-05-23 Change REF to 10 mV.
    This allows a decoder in 3 parallery connected track circuits to be
    safely detected (e.g. a loco shorts neighbour track circuits).
2024-05-25 Add bootloader as a copy of main application.
2024-06-22 Bootloader: add dwt_delay & eeprom libraries.
2024-06-22 Bootloader: add assert.h.
2024-06-22 Bootloader: add gpio.[ch].
2024-06-22 Bootloader compilable.
2024-06-22 Bootloader: use LL library for clock initialization.
2024-06-22 Bootloader: use LL library for GPIO.
2024-06-22 Bootloader: copy MTBbus sources, prepare for LL.
2024-07-21 Bootloader: make GPIO work.
2024-07-21 Bootloader: call 'fail' on unknown interrupt.
2024-07-21 Bootloader: make reading of inputs work.
2024-07-23 Bootloader: add openocd config.
2024-07-25 Bootloader: use LL library only.
2024-07-25 Bootloader: add polling mtbbus driver.
2024-07-26 Add own flash libray.
    The library is basically a few functions taken from STM32 HAL
    stm32f1xx_hal_flash.[ch] & stm32f1xx_hal_flash_ex.[ch].
2024-07-26 Bootloader: try to make timer 3 work.
2024-07-29 Bootloader: blink with green LED @ 500 ms.
2024-08-01 Bootloader: add missing CLK setting.
2024-08-01 Bootloader: make mtb addr reading work.
    I don't know why it didn't work before.
2024-08-01 Bootloader: remove handlers for non-existing interrupts.
2024-08-01 Bootloader: define USE_FULL_ASSERT in Makefile.
    This ensures all files being compiled get the right definition.
2024-08-01 Bootloader: make dwt delay work.
    Add own copy of a library, remove if, add initialization.
2024-08-01 Bootloader: USART3 is MTBBUS_USART (add new constant).
2024-08-01 Bootloader: proper interrupt handling.
2024-08-01 Stop receiving when new 9bit=1 received.
2024-08-01 Bootloader: fix typos, add speed mockup.
2024-08-01 Bootloader: make mocked-eeprom reading work.

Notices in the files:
pcb/dcc.kicad_sch:
Released under the Creative Commons Attribution-ShareAlike 4.0 License
